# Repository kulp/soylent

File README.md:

# soylent

`soylent` is an "aspirational" (i.e. entirely untested, and designed by an electronics neophyte) hardware design for a tiny hardware modem for the TI Silent 707 briefcase teletype from the [Texas Instruments Silent 700 series](https://en.wikipedia.org/wiki/Silent_700).

The teletype speaks 300-baud [FSK](https://en.wikipedia.org/wiki/Frequency-shift_keying) using the [Bell 103 dataset](https://en.wikipedia.org/wiki/Bell_103_modem). The modem is designed to connect directly to the acoustic-coupler interface of the teletype, which supplies power to the modem as well as providing the FSK audio signal. The modem is designed to implement full-duplex translation between the FSK signal and a minimal [RS-232](https://en.wikipedia.org/wiki/RS-232) serial connection at 300bps.

The intention is for the [tynsel](https://github.com/kulp/tynsel) project to supply a software implementation for the [AVR microcontroller](https://www.microchip.com/wwwproducts/en/ATTINY412) in the `soylent` design. For now, `soylent` serves mainly as a playground for the author to learn [KiCad](https://kicad-pcb.org).

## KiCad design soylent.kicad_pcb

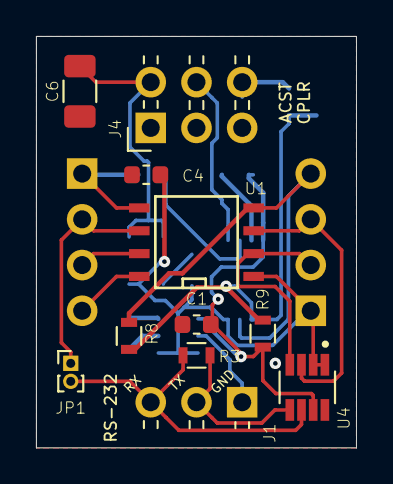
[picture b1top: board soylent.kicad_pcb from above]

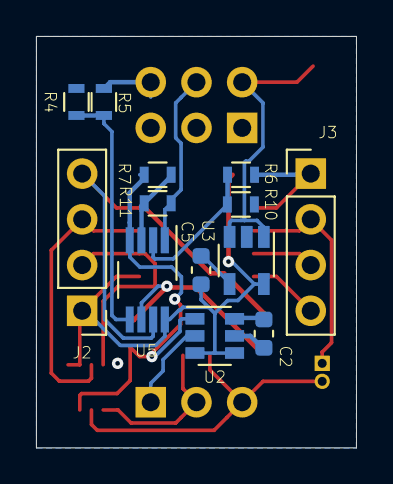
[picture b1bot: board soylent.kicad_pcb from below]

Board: 2 copper layers, 17.8 x 22.9 mm, 24 parts (13 on the bottom side), 21 nets.

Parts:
C1, C4: 2.2u; C_0603_1608Metric
C2: 1u; C_0603_1608Metric
C5: 0.01u; C_0603_1608Metric
C6: 47u; C_1206_3216Metric
J1: Conn_01x03; Pin_Header_Angled_1x03_Pitch2.54mm
J2, J3: Conn_01x04; Pin_Header_Straight_1x04_Pitch2.54mm
J4: ACST CPLR; Pin_Header_Angled_2x03_Pitch2.54mm
JP1: Jumper_2_Bridged; PinHeader_1x02_P1.00mm_Vertical
R3: 4k7; R_0603
R4, R5, R6, R7, R8, R9, R10, R11: 50k; R_0603
U1: ATtiny202-SS; SOIC-8-N
U2: LM2776; SOT-23-6
U3: LT1761-5; TSOT-23-5
U4: MAX3314EEKA-T; SOT65P280X145-8N
U5: LM2904; VSSOP-8_3.0x3.0mm_P0.65mm

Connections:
/PA3: J3.3, U1.7
/Power Regulation/+VDC: C6.1, J4.2, U3.1, U3.3
/RD: J1.3, JP1.2, R3.1, U4.6
/RX: J2.3, U1.3, U4.3
/TD: J1.2, R3.2, U4.5
/TTY interface/AIN: J4.6, R5.1
/TTY interface/AOUT: J4.4, R11.1, U5.1
/TX: J2.2, U1.2, U4.4
/UPDI: J3.2, JP1.1, U1.6
/WIN: J2.4, R8.2, U1.4, U5.7
/WOUT: J3.1, R6.2, U1.5
GND: C1.1, C4.1, C6.2, J1.1, J3.4, J4.5, R4.2, R10.1, U1.8, U2.2, U3.2, U4.8
unnamed: C2.1, U2.5
unnamed: C2.2, U2.6
unnamed: C5.1, U3.4
unnamed: R4.1, R5.2, U5.5
unnamed: R8.1, R9.2, U5.6
unnamed: R6.1, R10.2, U5.2
unnamed: R7.1, R11.2, U5.3
VDD: C4.2, C5.2, J2.1, U1.1, U2.3, U2.4, U3.5, U4.1, U4.2, U5.8
VEE: C1.2, R7.2, R9.1, U2.1, U4.7, U5.4

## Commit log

2019-11-26 Initial empty commit
2019-11-26 Reorganize level conversion
2019-11-26 Add missing base resistors
2019-11-26 Assign footprints
2019-11-26 Label breakout section
2019-11-26 Switch to 0603 for resistors
2019-11-26 Complete routing
2019-11-26 Routing tweaks
2019-11-26 Resquare ground zone
2019-11-26 Add GND via and fill
2019-11-26 Add voltage regulator circuit
2019-11-26 Annotate schematic
2019-11-26 Route regulator
2019-11-26 Routing tweaks, unfill
2019-11-26 Move labels a bit
2019-11-26 Add explicit jumper wire
2019-11-26 Cosmetic moving of pads
2019-11-26 Pick footprints for remaining items
2019-11-26 Rip up, add remaining components
2019-11-27 Routed, but ugly
2019-11-27 Routed, less ugly
2019-11-27 Beautifying ground planes
2019-11-27 Partial routing
2019-11-27 Removed another via
2019-11-27 Reduce vias once more
2019-11-27 Cleanup and prep for TTY I/F
2019-11-27 Leaving more space
2019-11-27 Lock headers and main chip
2019-11-27 Ground plane work, removing a via
2019-11-27 Move breakout traces to bottom layer
2019-11-27 Add Vdd and GND labels
2019-11-27 Rearranging labels
2019-11-27 Tweak a corner
2019-11-27 Adding components for TTY
2019-11-27 More vias
2019-11-27 Hook up analog in
2019-11-27 Make whole regulator disconnectable
2019-11-27 Space things out a bit and reroute
2019-11-27 Add a box for parasitic power
2019-11-27 Full ground plane restored, with one via
2019-11-27 Placing some TTY I/F components in ratsnest
2019-11-27 Fully routed, and ugly
2019-11-27 Remove gaps in ground plane
2019-11-27 Alternative routing
2019-11-27 Mark no-connections
2019-11-27 Swap analog lines and reroute
2019-11-27 Insert a resistor on output
2019-11-27 Switch to an RC filter
    http://sim.okawa-denshi.jp/en/CRtool.php
    fc = 4080.8959767153[Hz]
2019-11-27 Drop a via
2019-11-27 Add edge cuts
2019-11-27 Shrink cuts and zones
2019-11-27 Rerouting with one fewer vias
2019-11-27 Use hand-soldering footprints more consistently
2019-11-27 Fix up ground plane fill
2019-11-27 Cosmetic replacement and rerouting
2019-11-27 Ground plane fixups
2019-11-27 Reroute, no extraneous vias
2019-11-27 Cosmetic rerouting
2019-11-27 Rename pads
2019-11-27 Add a jumper for UPDI inhibit
2019-11-29 Correct bad footprint
2019-11-29 Shift up for ground plane contiguity
2019-11-29 Swap PNP and NPN and reroute
2019-11-29 Un-tweak routing
2019-11-29 Making more room on the schematic
2019-11-29 Tweak schematic cosmetics
2019-11-29 Rotate Q2 too
2019-11-29 Cosmetic routing tweaks
2019-11-29 Rotate Q3 for better routing
2019-11-29 Add a transistor to simulate mic
2019-11-29 Ground plane fixed up
2019-11-29 Routing, needs ground plane work
2019-11-29 Add bypass for UPDI disconnect
2019-11-29 Use fat traces for charge pump
2019-11-29 Rotate regulator for routing and fit
2019-11-29 Use fat traces for +5V supply caps
2019-11-29 Rotations and rerouting
2019-11-29 Reworking RS-232 interface
2019-11-29 Routed nicely
2019-11-29 Cosmetic changes to ground plane
2019-11-29 Add charge pump for a -5V Vee
2019-11-29 Move references around
2019-11-30 Shrink and move filter/driver
    Fix a bug with an inadvertent connection to RX from WIN, too
2019-11-30 Connect WIN wire that was dangling
2019-11-30 Fit into a smaller space
2019-11-30 Inline a voltage divider into op-amp feedback
2019-11-30 Shrink boxes
2019-11-30 Arbitrary rerouting in search of a cure
2019-11-30 Move origins
2019-11-30 Draw a box for the level shifter
2019-11-30 Wiring up opamp offsetter
2019-11-30 Shrink cut lines
2019-11-30 Replace a diagonal wire
2019-11-30 Shrink zones
2019-11-30 Shrink required board area
2019-11-30 Add and route trimmer pot
2019-11-30 Minor prettification
2019-11-30 Set nominal value for trimmer
2019-11-30 Add a ground via
2019-11-30 Address DRC findings
2019-12-02 Start using correct pinouts
2019-12-02 Perform automated cleanup
2019-12-02 More minor cleanup
2019-12-02 Shrink board outline
2019-12-02 Use all pins of trimmer pot
2019-12-02 Assign footprint for new header
2019-12-02 Shrink copper zones
2019-12-02 Use TTY-provided power
2019-12-02 Straw-man re-placement
2019-12-02 Rerouting, still in progress
2019-12-02 Drop solder jumpers and reroute
2019-12-02 Switch to three-pin header for RS-232
2019-12-02 Reroute for new regulator
2019-12-02 Bring DB-9 close and lock it
2019-12-02 Bring headers close and lock them
2019-12-02 Hook up new power supply on PCB
2019-12-02 More rats-nest straw-man placement
2019-12-02 Set up new header on PCB
2019-12-02 Rearranging for adjacency
2019-12-02 Add the legs of the spider
2019-12-02 Switch to a 5V regulator from +VDC
2019-12-03 Use smaller jumper
2019-12-03 Experimenting with hierarchical sheets
2019-12-03 Add basic .gitignore file
2019-12-03 Add lib-table files
2019-12-03 Strawman placement ready for strawman routing
2019-12-03 Straw-man placement
2019-12-03 Strawman routing complete
2019-12-03 Placing headers again
2019-12-03 Strawman routing
2019-12-03 Tweaks to the strawman routing
2019-12-03 Add zones
2019-12-03 Fix up broken wire
2019-12-03 Flip a resistor
2019-12-03 Experimental shrinkage
2019-12-04 Use OSHPark minima
2019-12-04 Add some more fixed track widths
2019-12-04 Try 8-mil traces
2019-12-04 Change to 10/12 ground planes
2019-12-04 Change to 8/10 fill zones
2019-12-07 Use MAX3180 for incoming RS-232
2019-12-07 Moving and shaking, with a weird extra via
2019-12-07 Rearranging components
2019-12-07 Flip pins onto back
2019-12-07 Correct some design rules violations
2019-12-07 Make cosmetic routing adjustments
2019-12-07 Tweaks, reconnect Vee
2019-12-07 Fix up ground plane cosmetics
2019-12-07 Fix up J1 reference
2019-12-07 Shrink reference text
2019-12-07 Shrink zones to cut lines
2019-12-07 Fix more 3D model paths
2019-12-07 Get rid of hand-soldering footprints in schematic too
2019-12-07 Implementing forced moves
2019-12-07 Put UPDI jumper back on top
2019-12-07 Add models for headers
2019-12-07 Enable all back layers, move references
2019-12-07 Fix up models for new footprints
2019-12-07 Restore fab parts of header footprints
2019-12-07 Checkpoint in reroute before MAX3314E
2019-12-07 Add libs for MAX3314E
2019-12-07 Reroute
2019-12-07 Remove silkscreen Fab for angled headers
2019-12-07 Flip serial connector and make it angled
2019-12-07 Fix up ground plane
2019-12-07 Expand to 0.75x0.85 inches
2019-12-07 Completely routed with new chips
2019-12-07 Change layer hiding
2019-12-07 Tweak reference locations
2019-12-07 Fix some 3D model paths
2019-12-07 Switch away from hand-soldered footprints
2019-12-07 Change model for 3-pin header
2019-12-07 Add labels for RS-232
    Also move JP1 to make room
2019-12-07 Add label for acoustic coupler
2019-12-09 Flip large cap onto top side
2019-12-09 Use a big 47uF cap on input to regulator
2019-12-09 Move labels
2019-12-09 Allow a better ground fill
2019-12-14 Adjust tty schematic cosmetically
2019-12-14 Flop power across Y axis
2019-12-14 Adjust cosmetics of power schematic
2019-12-14 Reconnect Vdd to TTY
2019-12-14 Obey some ERC findings
2019-12-14 Tweak power schematic
2019-12-14 Make more cosmetic changes to top level
2019-12-14 Rearrange pins cosmetically
2019-12-14 Align power wires cosmetically
2019-12-14 Adjust power cosmetics
2020-01-03 Add a 640px JPEG of the 3d-rendered board
2020-01-03 Show 3d rendering of soylent PCB
2020-01-03 Create README.md (#1)
    * Create README.md
    * Show a 640px JPEG of the 3D-rendered PCB
2023-01-22 Update to KiCad 6.0.10 formats
    These updates were done automatically by KiCad, with no other changes.
2025-04-17 Upgrade formats using KiCad 9.0.1
2025-04-17 Ignore modern backup directories
2025-04-17 Import library files previously used but not committed
2025-04-17 Migrate libraries
2025-04-17 Remove library cache
2025-04-17 Fix path
2025-04-17 Migrate footprints
